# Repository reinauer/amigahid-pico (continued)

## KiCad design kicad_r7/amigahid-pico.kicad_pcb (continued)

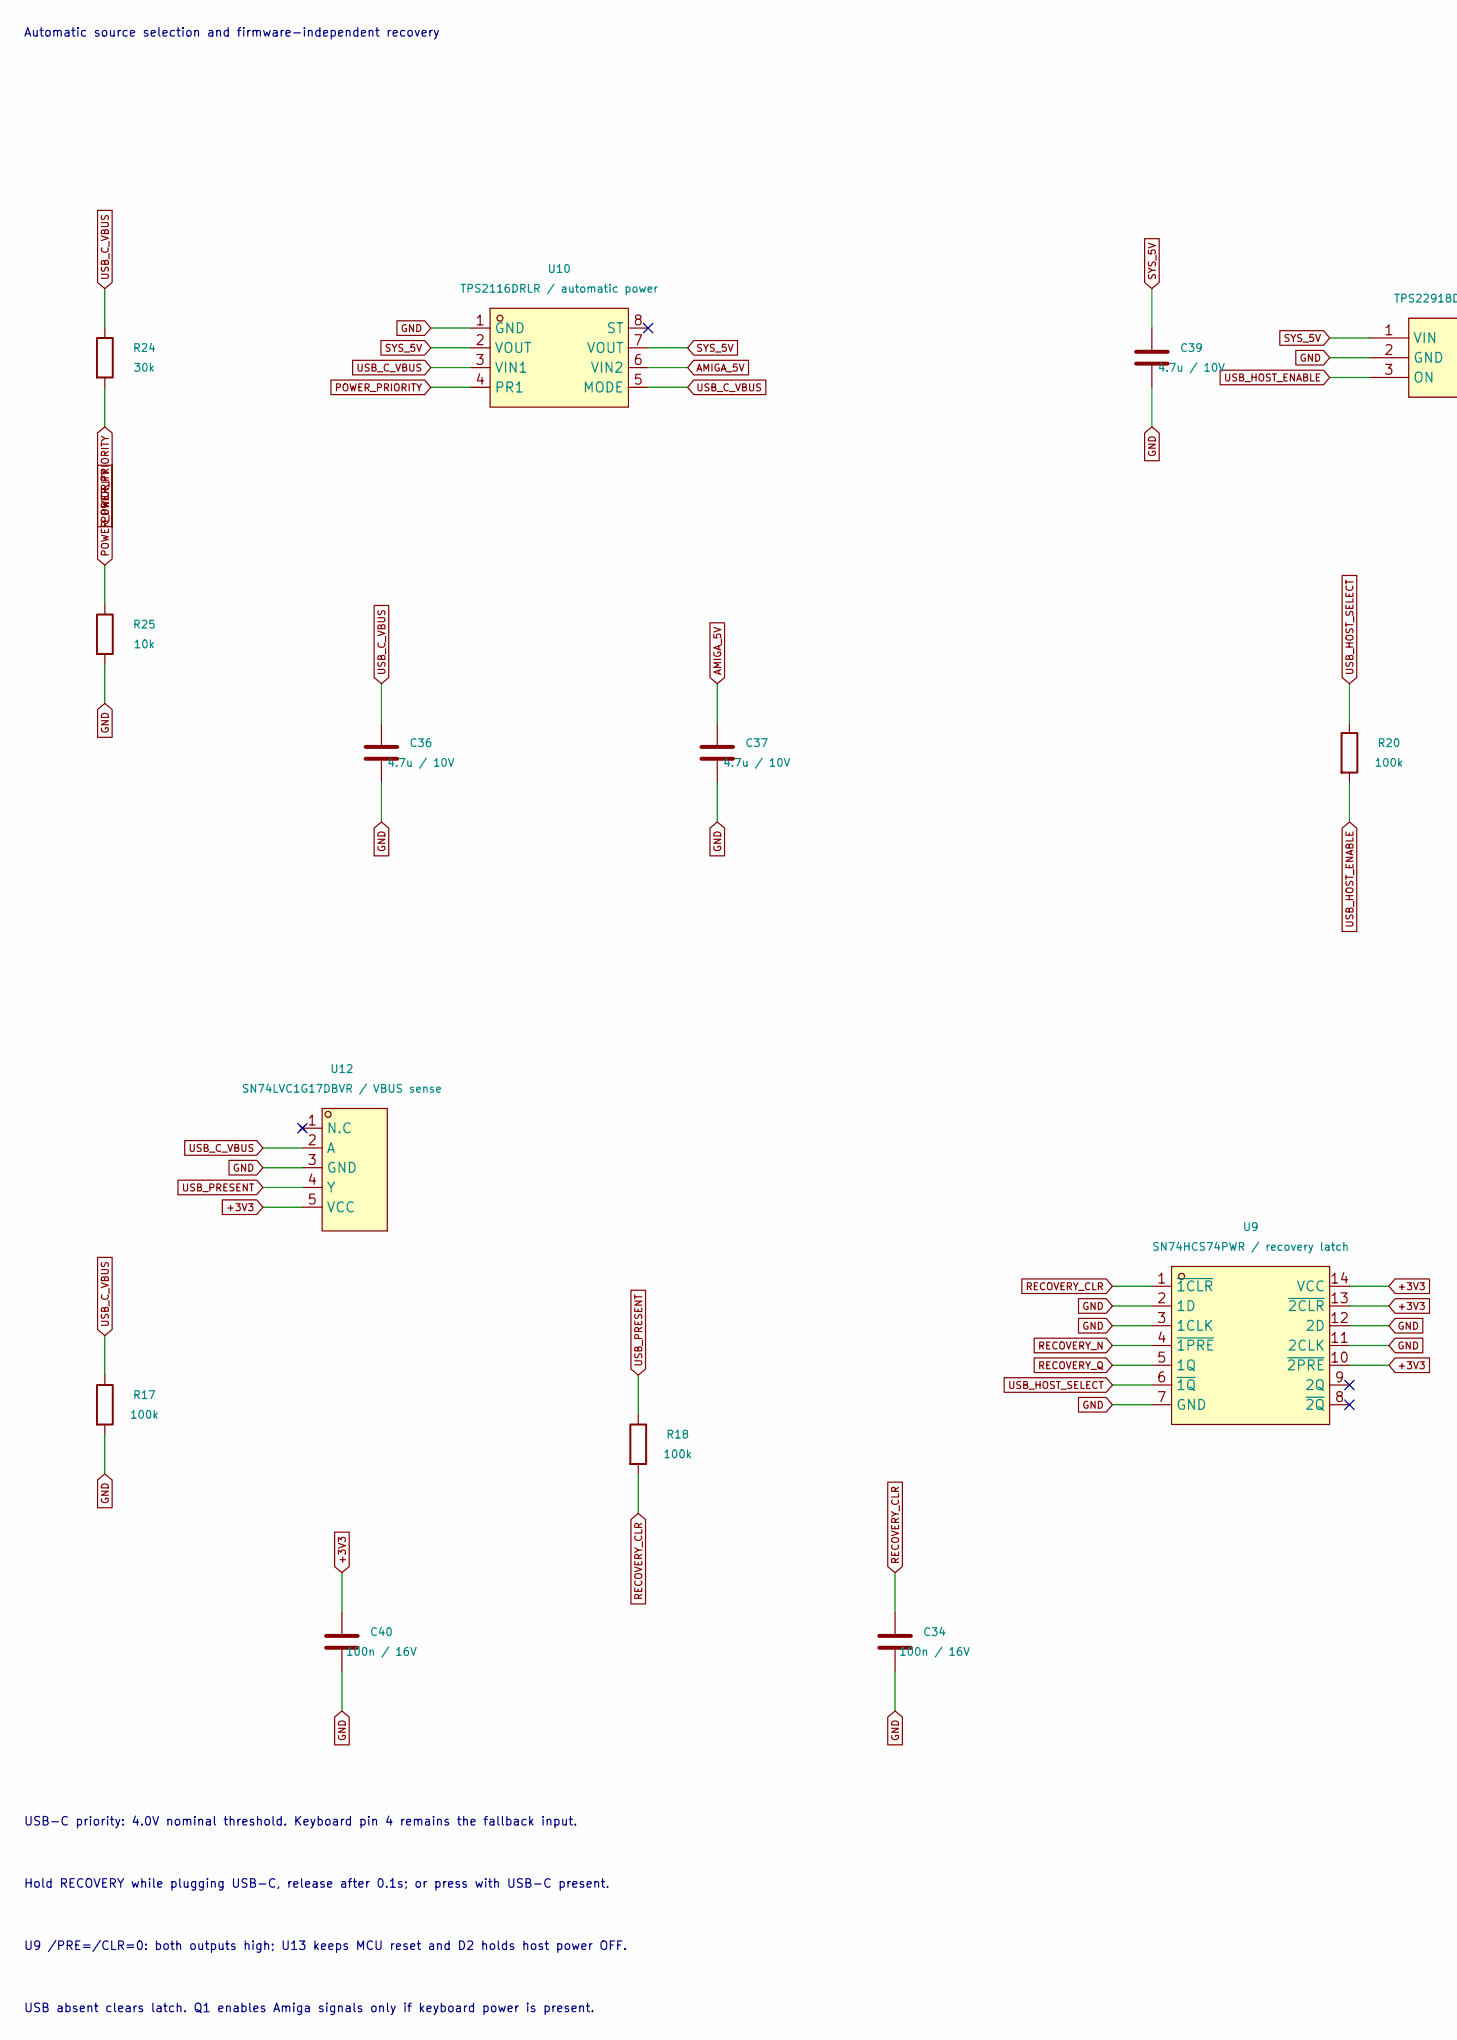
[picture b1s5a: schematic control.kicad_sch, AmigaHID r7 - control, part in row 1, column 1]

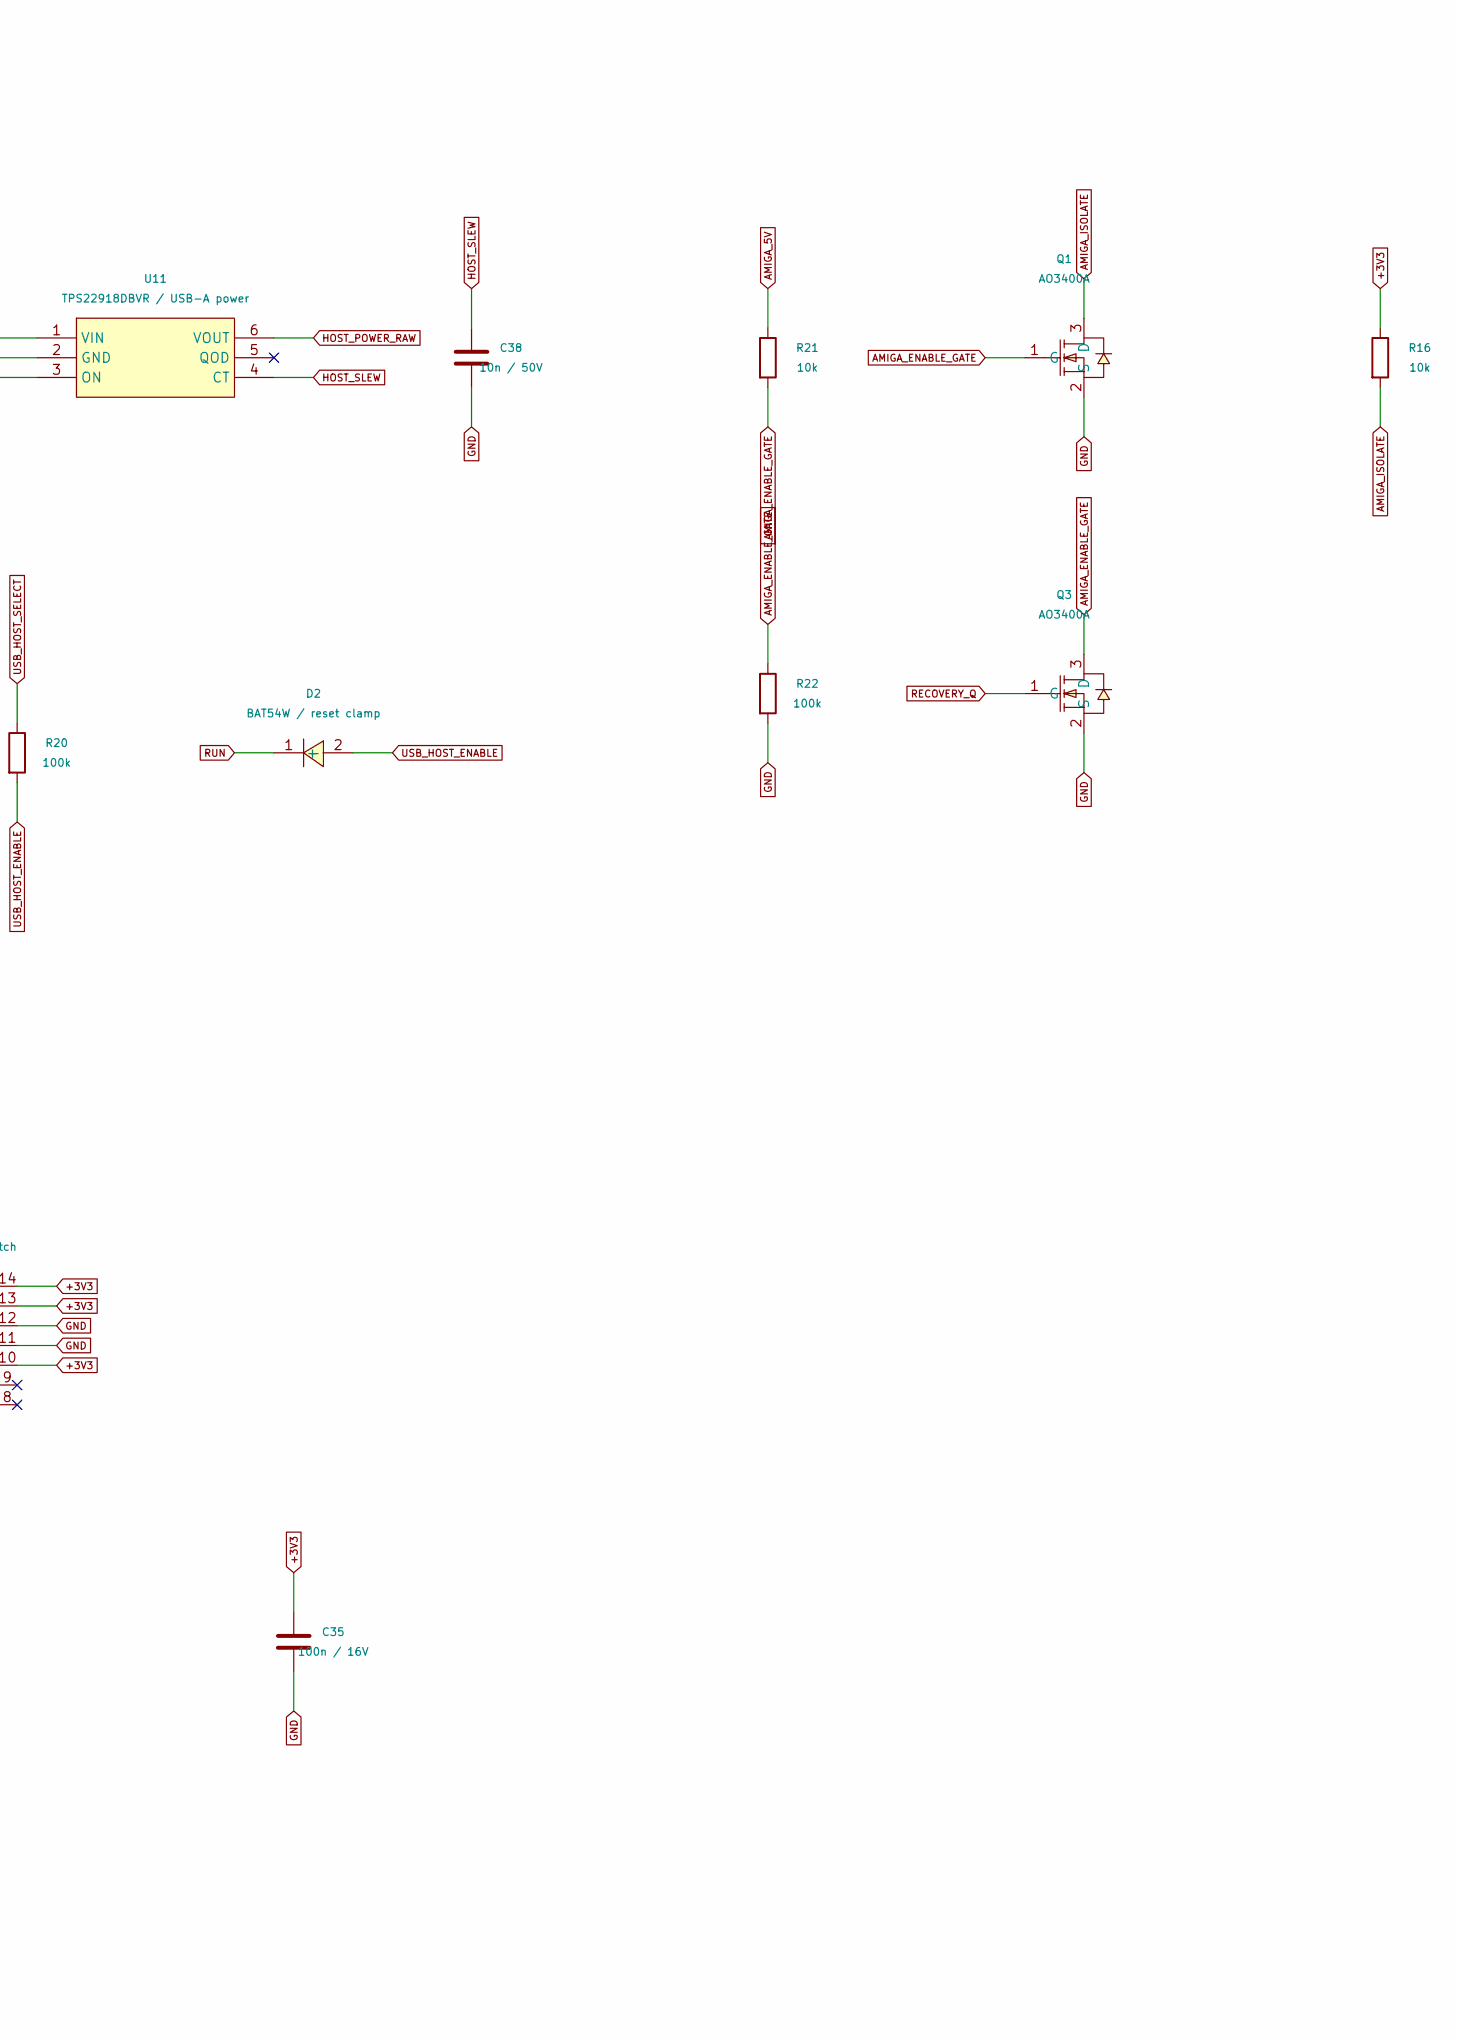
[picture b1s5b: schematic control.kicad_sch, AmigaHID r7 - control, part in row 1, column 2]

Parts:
C34, C35, C40: 100n / 16V; C0402; MPN CL05B104KO5NNNC; LCSC Part # C1525
C36, C37, C39: 4.7u / 10V; C0402; MPN CL05A475MP5NRNC; LCSC Part # C23733
C38: 10n / 50V; C0402; MPN CL05B103KB5NNNC; LCSC Part # C15195
D2: BAT54W / reset clamp; SOD-123_L2.8-W1.8-LS3.7-RD; MPN BAT54W; LCSC Part # C131469
Q1, Q3: AO3400A; SOT-23-3_L2.9-W1.3-P1.90-LS2.4-BR; MPN AO3400A; LCSC Part # C20917
R16, R21, R25: 10k; R0402; MPN 0402WGF1002TCE; LCSC Part # C25744
R17, R18, R20, R22: 100k; R0402; MPN 0402WGF1003TCE; LCSC Part # C25741
R24: 30k; R0402; MPN 0402WGF3002TCE; LCSC Part # C25776
U9: SN74HCS74PWR / recovery latch; TSSOP-14_L5.0-W4.5-P0.65-LS6.4-BL; MPN SN74HCS74PWR; LCSC Part # C2866652
U10: TPS2116DRLR / automatic power; SOT-583-8_L2.1-W1.6-P0.50-LS1.6-BL; MPN TPS2116DRLR; LCSC Part # C3235557
U11: TPS22918DBVR / USB-A power; SOT-23-6_L2.9-W1.6-P0.95-LS2.8-BR; MPN TPS22918DBVR; LCSC Part # C131941
U12: SN74LVC1G17DBVR / VBUS sense; SOT-23-5_L3.0-W1.7-P0.95-LS2.8-BR; MPN SN74LVC1G17DBVR; LCSC Part # C7836

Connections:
+3V3: C35.1, C40.1, R16.1, U9.10 (~2PRE), U9.13 (~2CLR), U9.14 (VCC), U12.5 (VCC); also elsewhere on the board
AMIGA_5V: C37.1, R21.1, U10.6 (VIN2); also elsewhere on the board
AMIGA_ENABLE_GATE: Q1.1 (G), Q3.3 (D), R21.2, R22.1
AMIGA_ISOLATE: Q1.3 (D), R16.2; also elsewhere on the board
GND: C34.2, C35.2, C36.2, C37.2, C38.2, C39.2, C40.2, Q1.2 (S), Q3.2 (S), R17.2, R22.2, R25.2, U9.2 (1D), U9.3 (1CLK), U9.7 (GND), U9.11 (2CLK), U9.12 (2D), U10.1 (GND), U11.2 (GND), U12.3 (GND); also elsewhere on the board
HOST_POWER_RAW: U11.6 (VOUT); also elsewhere on the board
HOST_SLEW: C38.1, U11.4 (CT)
POWER_PRIORITY: R24.2, R25.1, U10.4 (PR1)
RECOVERY_CLR: C34.1, R18.2, U9.1 (~1CLR)
RECOVERY_N: U9.4 (~1PRE); also elsewhere on the board
RECOVERY_Q: Q3.1 (G), U9.5 (1Q); also elsewhere on the board
RUN: D2.1 (-); also elsewhere on the board
SYS_5V: C39.1, U10.2 (VOUT), U10.7 (VOUT), U11.1 (VIN); also elsewhere on the board
USB_C_VBUS: C36.1, R17.1, R24.1, U10.3 (VIN1), U10.5 (MODE), U12.2 (A); also elsewhere on the board
USB_HOST_ENABLE: D2.2 (+), R20.2, U11.3 (ON)
USB_HOST_SELECT: R20.1, U9.6 (~1Q); also elsewhere on the board
USB_PRESENT: R18.1, U12.4 (Y)

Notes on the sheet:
Automatic source selection and firmware-independent recovery
USB-C priority: 4.0V nominal threshold. Keyboard pin 4 remains the fallback input.
Hold RECOVERY while plugging USB-C, release after 0.1s; or press with USB-C present.
U9 /PRE=/CLR=0: both outputs high; U13 keeps MCU reset and D2 holds host power OFF.
USB absent clears latch. Q1 enables Amiga signals only if keyboard power is present.

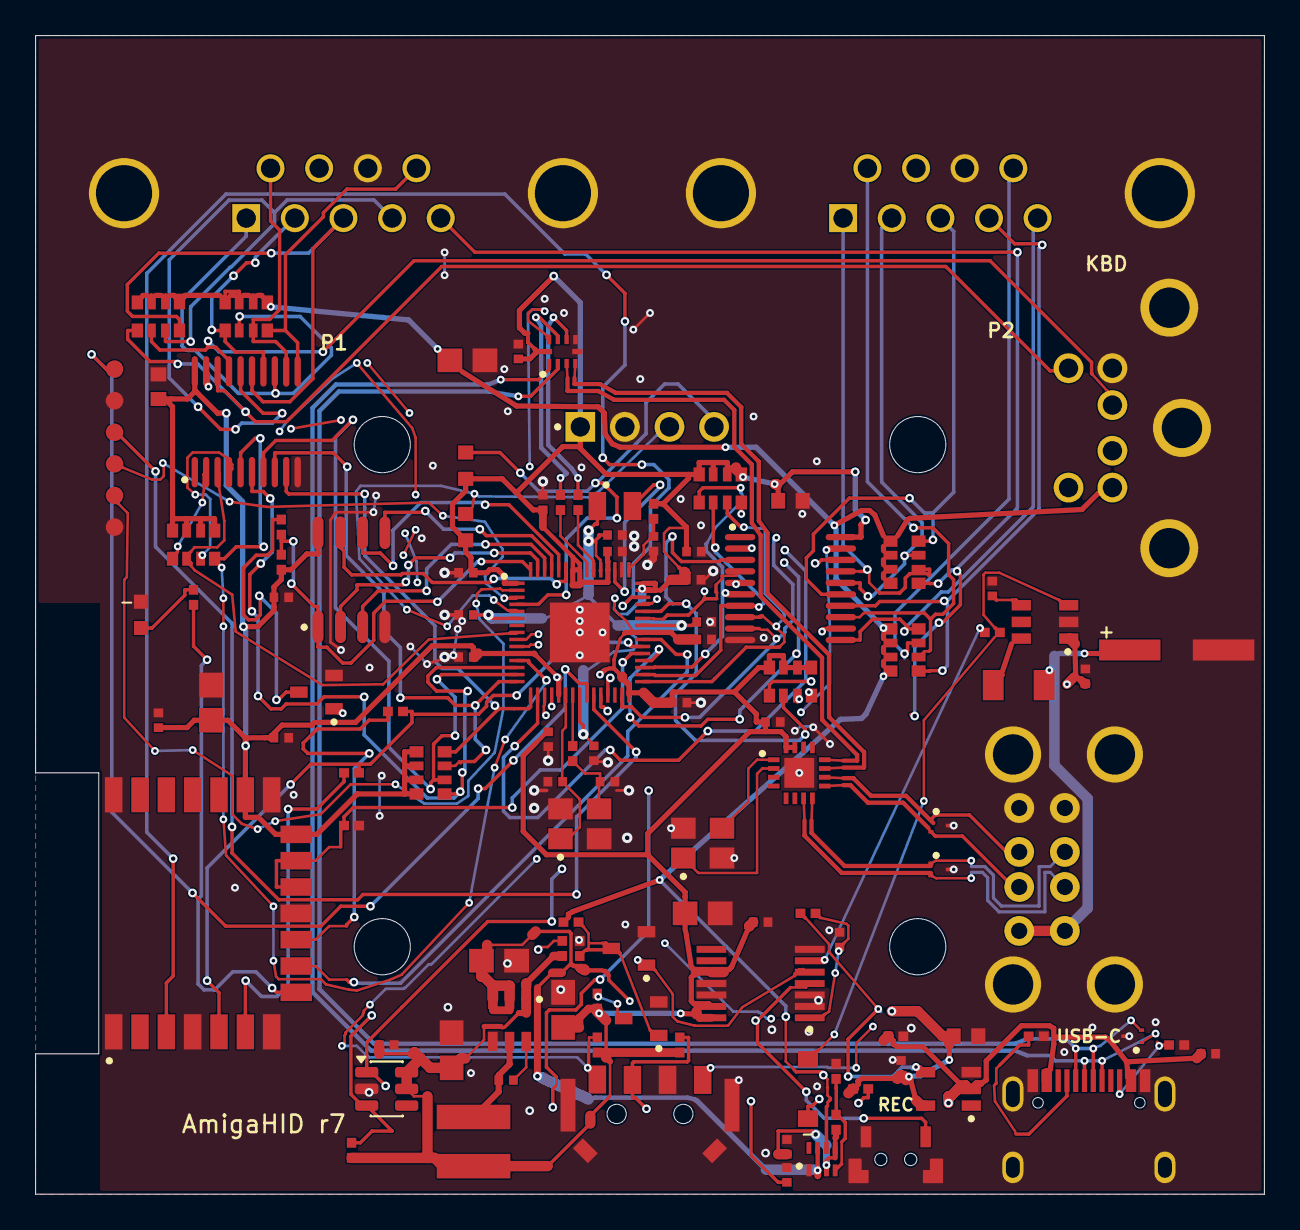
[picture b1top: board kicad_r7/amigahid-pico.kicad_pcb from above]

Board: 4 copper layers, 70.0 x 66.0 mm, 115 parts (0 on the bottom side), 98 nets.

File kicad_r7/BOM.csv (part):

Reference,Value,LCSC Part #,MPN,Manufacturer,Footprint,Datasheet,Source,Notes,Function
U2,SN74CB3T3245PWR,C15298,SN74CB3T3245PWR,TI(德州仪器),lcsc:TSSOP-20_L6.5-W4.4-P0.65-LS6.4-BL,https://lcsc.com/product-detail/Logic-ICs_TI_SN74CB3T3245PWR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,https://www.lcsc.com/product-detail/C15298.html,3V3 bus switch with Ioff; disabled when Amiga keyboard power is absent or ROM recovery is selected. GPIO drives LOW or releases.,
U3,SN74CB3T3245PWR,C15298,SN74CB3T3245PWR,TI(德州仪器),lcsc:TSSOP-20_L6.5-W4.4-P0.65-LS6.4-BL,https://lcsc.com/product-detail/Logic-ICs_TI_SN74CB3T3245PWR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,https://www.lcsc.com/product-detail/C15298.html,3V3 bus switch with Ioff; disabled when Amiga keyboard power is absent or ROM recovery is selected. GPIO drives LOW or releases.,
RN1,4x10k isolated,C192513,EXB38V103JV,PANASONIC,lcsc:RES-ARRAY-SMD_0603-8P-L3.2-W1.6-BL,https://datasheet.lcsc.com/datasheet/pdf/45e874bd934a49da039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,https://www.lcsc.com/product-detail/C192513.html,Retained r6 electrical function; LCSC package reviewed for r7.,
RN2,4x10k isolated,C192513,EXB38V103JV,PANASONIC,lcsc:RES-ARRAY-SMD_0603-8P-L3.2-W1.6-BL,https://datasheet.lcsc.com/datasheet/pdf/45e874bd934a49da039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,https://www.lcsc.com/product-detail/C192513.html,Retained r6 electrical function; LCSC package reviewed for r7.,
RN3,4x10k isolated,C192513,EXB38V103JV,PANASONIC,lcsc:RES-ARRAY-SMD_0603-8P-L3.2-W1.6-BL,https://datasheet.lcsc.com/datasheet/pdf/45e874bd934a49da039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,https://www.lcsc.com/product-detail/C192513.html,Retained r6 electrical function; LCSC package reviewed for r7.,
RN4,4x10k isolated,C192513,EXB38V103JV,PANASONIC,lcsc:RES-ARRAY-SMD_0603-8P-L3.2-W1.6-BL,https://datasheet.lcsc.com/datasheet/pdf/45e874bd934a49da039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,https://www.lcsc.com/product-detail/C192513.html,Retained r6 electrical function; LCSC package reviewed for r7.,
RN6,4x10k isolated,C192513,EXB38V103JV,PANASONIC,lcsc:RES-ARRAY-SMD_0603-8P-L3.2-W1.6-BL,https://datasheet.lcsc.com/datasheet/pdf/45e874bd934a49da039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,https://www.lcsc.com/product-detail/C192513.html,Retained r6 electrical function; LCSC package reviewed for r7.,
RN7,4x10k isolated,C192513,EXB38V103JV,PANASONIC,lcsc:RES-ARRAY-SMD_0603-8P-L3.2-W1.6-BL,https://datasheet.lcsc.com/datasheet/pdf/45e874bd934a49da039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,https://www.lcsc.com/product-detail/C192513.html,Retained r6 electrical function; LCSC package reviewed for r7.,
RN8,4x10k isolated,C192513,EXB38V103JV,PANASONIC,lcsc:RES-ARRAY-SMD_0603-8P-L3.2-W1.6-BL,https://datasheet.lcsc.com/datasheet/pdf/45e874bd934a49da039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,https://www.lcsc.com/product-detail/C192513.html,Retained r6 electrical function; LCSC package reviewed for r7.,
RN9,4x10k isolated,C192513,EXB38V103JV,PANASONIC,lcsc:RES-ARRAY-SMD_0603-8P-L3.2-W1.6-BL,https://datasheet.lcsc.com/datasheet/pdf/45e874bd934a49da039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,https://www.lcsc.com/product-detail/C192513.html,Retained r6 electrical function; LCSC package reviewed for r7.,
J3,OLED 3V3 I2C,C7509546,DS1023-1x4SF11,CONNFLY Elec,lcsc:HDR-TH_4P-P2.54-V-F,https://datasheet.lcsc.com/datasheet/pdf/e746529444b0a48d4f2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,https://www.lcsc.com/product-detail/C7509546.html,Retained r6 electrical function; LCSC package reviewed for r7.,
J4,Stacked USB-A / two host ports,C2341,907-111A1012D10200,精拓金,lcsc:USB-A-TH_USB-M-51,https://lcsc.com/product-detail/USB-Connectors_USB-A-F-Doubl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,https://www.lcsc.com/product-detail/C2341.html,Both USB-A ports share the Amiga-only 500mA PTC branch. See stock-check.json for dated availability. Confirm the through-hole soldering profile before assembly.,
J5,DE9 female to Amiga,C50380980,LCK-205A09FJ2A00B1A,LCKELEC,lcsc:DE9_Female_C50380980,https://datasheet.lcsc.com/datasheet/pdf/98ad6adf9b8970a1124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,https://www.lcsc.com/product-detail/C50380980.html,Retained r6 electrical function; LCSC package reviewed for r7.,
J6,DE9 female to Amiga,C50380980,LCK-205A09FJ2A00B1A,LCKELEC,lcsc:DE9_Female_C50380980,https://datasheet.lcsc.com/datasheet/pdf/98ad6adf9b8970a1124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,https://www.lcsc.com/product-detail/C50380980.html,Retained r6 electrical function; LCSC package reviewed for r7.,
J7,A4000 keyboard link,C77848,DS1093-01-PN60,CONNFLY,lcsc:CONN-TH_DS1093-01-PN60,https://datasheet.lcsc.com/datasheet/pdf/91b259a35bf42e0e40c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,https://www.lcsc.com/product-detail/C77848.html,"C77848 replaces unavailable r6 HOOYA C7428703. Supplier drawing sets 13.70mm shield pitch, 2.30mm shield holes and 4.78mm central-tab setback. Standard mini-DIN numbering retained; front face unchanged.",
F1,500mA hold PTC,C75464,MF-NSMF050-2,BOURNS,lcsc:F1206,https://datasheet.lcsc.com/datasheet/pdf/9de05d43c1e248c08c0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,https://www.lcsc.com/product-detail/C75464.html,Shared 500mA hold PTC for both USB-A ports; fed from selected source through U11. This does not increase the keyboard-port current rating.,
C1,100n / 50V,C14663,CC0603KRX7R9BB104,YAGEO,lcsc:C0603,https://datasheet.lcsc.com/datasheet/pdf/23ccee80ee542e7cf15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,https://www.lcsc.com/product-detail/C14663.html,Retained r6 electrical function; LCSC package reviewed for r7.,
C2,100n / 50V,C14663,CC0603KRX7R9BB104,YAGEO,lcsc:C0603,https://datasheet.lcsc.com/datasheet/pdf/23ccee80ee542e7cf15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,https://www.lcsc.com/product-detail/C14663.html,Retained r6 electrical function; LCSC package reviewed for r7.,
C3,10u / 25V,C15850,CL21A106KAYNNNE,Samsung Electro-Mechanics,lcsc:C0805,https://datasheet.lcsc.com/datasheet/pdf/02336ea48ea44ca18c7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,https://www.lcsc.com/product-detail/C15850.html,Retained r6 electrical function; LCSC package reviewed for r7.,
C4,220u / 10V polymer,C19270700,JBLM2221M010C058RTM,DMBJ,lcsc:CAP-SMD_BD6.3-L6.6-W6.6-LS7.4-FD,https://datasheet.lcsc.com/datasheet/pdf/25cd8a66a5cec751f28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,https://www.lcsc.com/product-detail/C19270700.html,"Shared USB-A bulk reservoir, 35mohm ESR at 100kHz. 176uF minimum at -20% initial tolerance. Amiga-only USB_5V branch; excluded from USB-C recovery load. Verify hot-plug droop and Amiga startup inrush.",
C5,100n / 50V,C14663,CC0603KRX7R9BB104,YAGEO,lcsc:C0603,https://datasheet.lcsc.com/datasheet/pdf/23ccee80ee542e7cf15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,https://www.lcsc.com/product-detail/C14663.html,Retained r6 electrical function; LCSC package reviewed for r7.,
R1,4.7k,C23162,0603WAF4701T5E,UNI-ROYAL,lcsc:R0603,https://datasheet.lcsc.com/datasheet/pdf/0a975aaa49b7c97f38a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,https://www.lcsc.com/product-detail/C23162.html,Retained r6 electrical function; LCSC package reviewed for r7.,
R2,4.7k,C23162,0603WAF4701T5E,UNI-ROYAL,lcsc:R0603,https://datasheet.lcsc.com/datasheet/pdf/0a975aaa49b7c97f38a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,https://www.lcsc.com/product-detail/C23162.html,Retained r6 electrical function; LCSC package reviewed for r7.,
U1,RP2350A,C42411118,RP2350A,Raspberry Pi(树莓派),lcsc:QFN-60_L7.0-W7.0-P0.40-TL-EP3.4,https://www.lcsc.com/datasheet/C42411118.pdf,https://www.lcsc.com/product-detail/C42411118.html,RP2350A QFN-60 plus exposed GND pad 61; GPIO map preserved from r6.,
U4,RMC20452T,C49451547,RMC20452T,Raspberry Pi(树莓派),lcsc:WIRELM-SMD_RMC20452T,https://www.lcsc.com/datasheet/C49451547.pdf,https://www.lcsc.com/product-detail/C49451547.html,"RM2 datasheet DS-6 Table 2: shared GP24 data/IRQ via 470R and 10k; GP23 enable, GP25 CS, GP29 CLK.",
U5,W25Q32JVSNIQ / 4MB,C5355146,W25Q32JVSNIQ,Winbond(华邦),lcsc:SOP-8_L4.9-W3.9-P1.27-LS6.0-BL,https://www.lcsc.com/datasheet/C5355146.pdf,https://www.lcsc.com/product-detail/C5355146.html,,
U6,AP63203WU-7 / 3V3,C780769,AP63203WU-7,DIODES(美台),lcsc:TSOT-26_L2.9-W1.6-P0.95-LS2.8-BL,https://www.lcsc.com/datasheet/C780769.pdf,https://www.lcsc.com/product-detail/C780769.html,"3V3 buck from diode-OR SYS_5V. Normal: Amiga power. Recovery: USB-C power. Verify minimum input after diode drop, inrush and USB recovery current.",
L1,3.3uH / dotted end = 1V1,C42411119,AOTA-B201610S3R3-101-T,ABRACON,lcsc:IND-SMD_L2.0-W1.6_AOTA-B201610S3R3-101-T,https://www.lcsc.com/datasheet/C42411119.pdf,https://www.lcsc.com/product-detail/C42411119.html,"Use marked Abracon part. Pad 1 (dot) goes to output, pad 2 to LX; follow Raspberry Pi R4-S1 regulator placement.",
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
